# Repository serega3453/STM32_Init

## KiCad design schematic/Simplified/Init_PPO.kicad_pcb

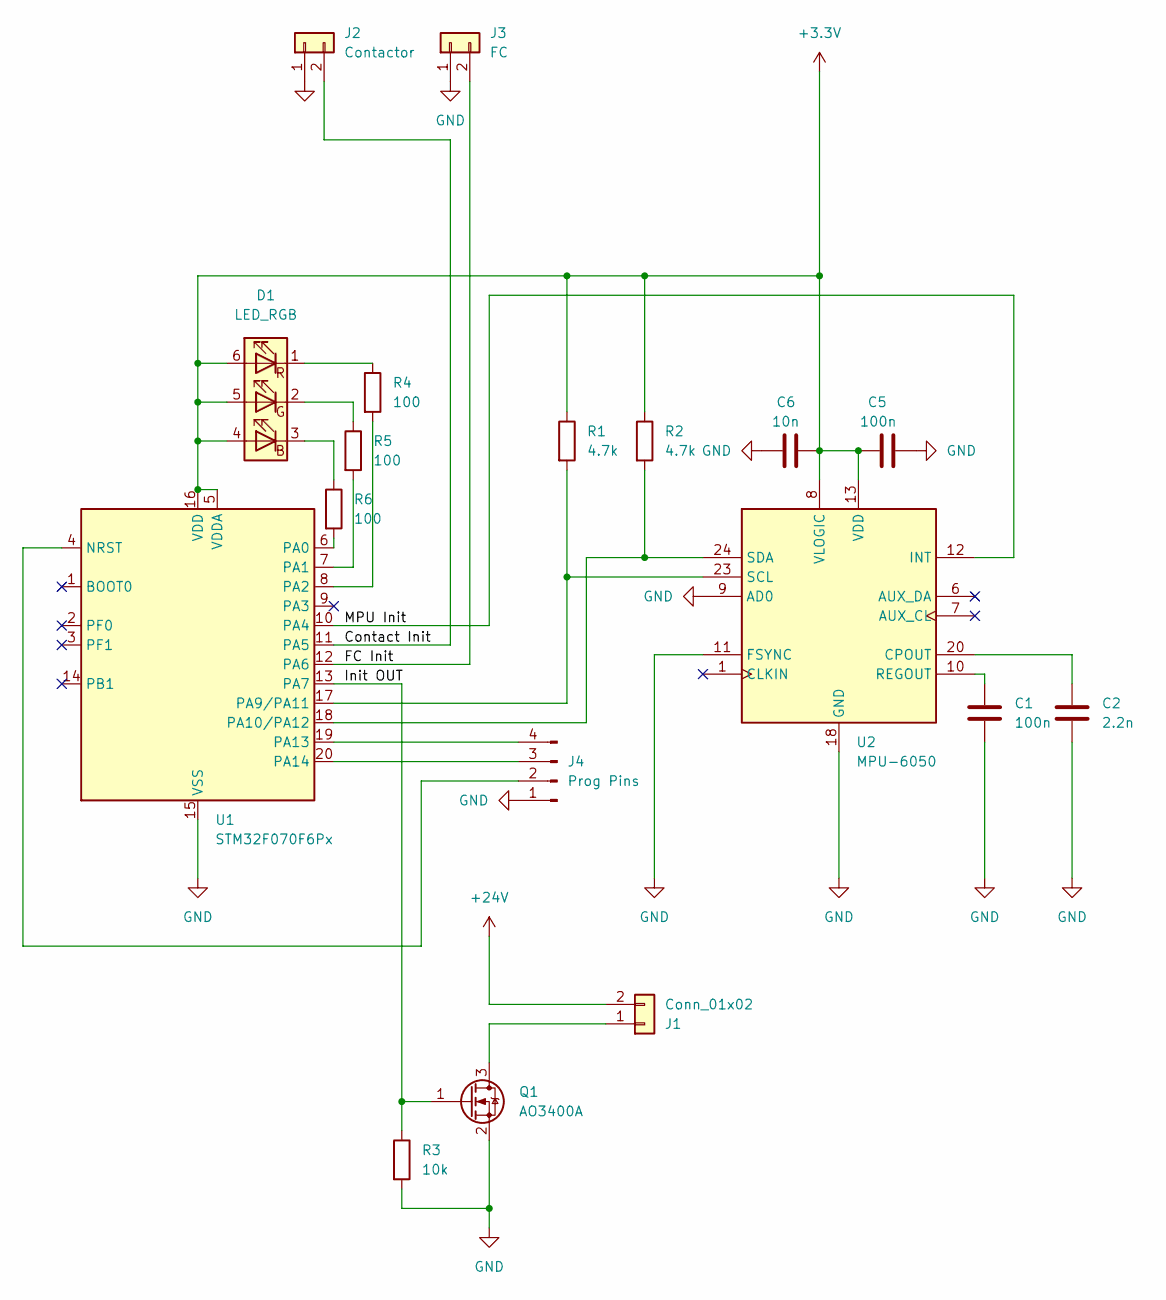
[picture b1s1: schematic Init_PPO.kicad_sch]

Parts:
C1, C5: 100n; C_0805_2012Metric_Pad1.18x1.45mm_HandSolder
C2: 2.2n; C_0805_2012Metric_Pad1.18x1.45mm_HandSolder
C6: 10n; C_0805_2012Metric_Pad1.18x1.45mm_HandSolder
D1: LED_RGB; LED_RGB_5050-6
J1: Conn_01x02; SolderWire-0.25sqmm_1x02_P4.5mm_D0.65mm_OD2mm
J2: Contactor; SolderWire-0.25sqmm_1x02_P4.5mm_D0.65mm_OD2mm
J3: FC; SolderWire-0.25sqmm_1x02_P4.5mm_D0.65mm_OD2mm
J4: Prog Pins
Q1: AO3400A; SOT-23
R1, R2: 4.7k; R_0805_2012Metric_Pad1.20x1.40mm_HandSolder
R3: 10k; R_0805_2012Metric_Pad1.20x1.40mm_HandSolder
R4, R5, R6: 100; R_0805_2012Metric_Pad1.20x1.40mm_HandSolder
U1: STM32F070F6Px; TSSOP-20_4.4x6.5mm_P0.65mm
U2: MPU-6050; InvenSense_QFN-24_4x4mm_P0.5mm

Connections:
+3.3V: C5.1, C6.2, D1.4 (BA), D1.5 (GA), D1.6 (RA), R1.1, R2.1, U1.5 (VDDA), U1.16 (VDD), U2.8 (VLOGIC), U2.13 (VDD)
+24V: J1.2
/Contact Init: J2.2, U1.11 (PA5)
/FC Init: J3.2, U1.12 (PA6)
/Init OUT: Q1.1 (G), R3.1, U1.13 (PA7)
/MPU Init: U1.10 (PA4), U2.12 (INT)
GND: C1.2, C2.2, C5.2, C6.1, J2.1, J3.1, J4.1, Q1.2 (S), R3.2, U1.15 (VSS), U2.9 (AD0), U2.11 (FSYNC), U2.18 (GND)
unnamed: D1.3 (BK), R6.1
unnamed: D1.2 (GK), R5.1
unnamed: D1.1 (RK), R4.1
unnamed: J1.1, Q1.3 (D)
unnamed: J4.2, U1.4 (NRST)
unnamed: J4.3, U1.20 (PA14)
unnamed: J4.4, U1.19 (PA13)
unnamed: R6.2, U1.6 (PA0)
unnamed: R5.2, U1.7 (PA1)
unnamed: R4.2, U1.8 (PA2)
unnamed: R1.2, U1.17 (PA9/PA11), U2.23 (SCL)
unnamed: R2.2, U1.18 (PA10/PA12), U2.24 (SDA)
unnamed: C2.1, U2.20 (CPOUT)
unnamed: C1.1, U2.10 (REGOUT)

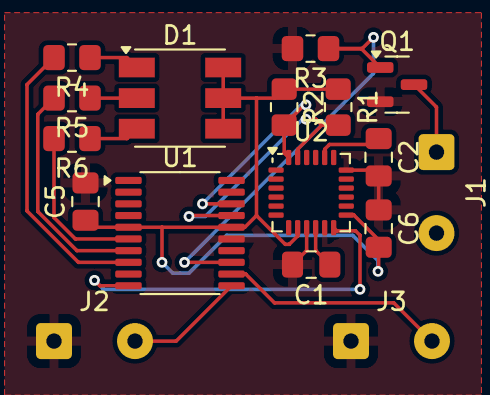
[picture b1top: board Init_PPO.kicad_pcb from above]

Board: 2 copper layers, 17 parts (0 on the bottom side), 17 nets.

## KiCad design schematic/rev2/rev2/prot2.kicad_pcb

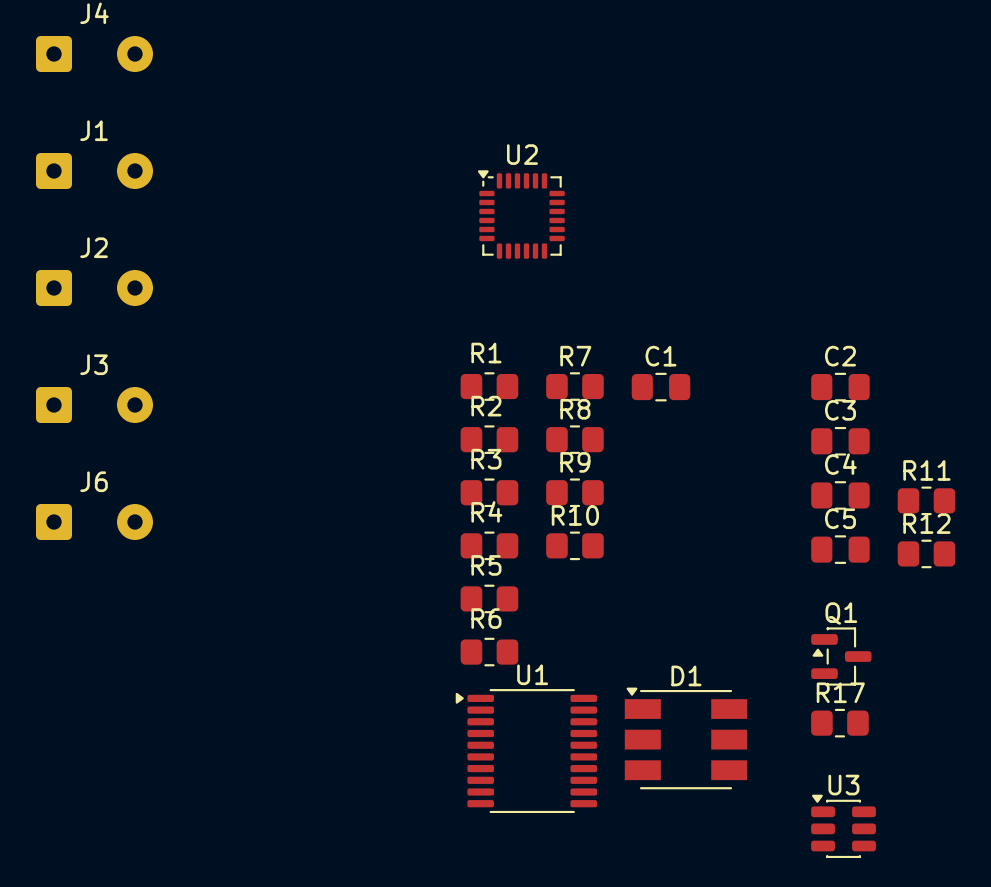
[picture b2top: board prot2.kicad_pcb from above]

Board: 2 copper layers, 28 parts (0 on the bottom side), 21 nets, no tracks yet.

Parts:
C1, C3, C4: 100n; C_0805_2012Metric_Pad1.18x1.45mm_HandSolder
C2: 10n; C_0805_2012Metric_Pad1.18x1.45mm_HandSolder
C5: 2.2n; C_0805_2012Metric_Pad1.18x1.45mm_HandSolder
D1: LED_RGB; LED_RGB_5050-6
J1: SAFE MODE; SolderWire-0.25sqmm_1x02_P4.5mm_D0.65mm_OD2mm
J2: Contactor; SolderWire-0.25sqmm_1x02_P4.5mm_D0.65mm_OD2mm
J3: FCU; SolderWire-0.25sqmm_1x02_P4.5mm_D0.65mm_OD2mm
J4: Power; SolderWire-0.25sqmm_1x02_P4.5mm_D0.65mm_OD2mm
J6: Load; SolderWire-0.25sqmm_1x02_P4.5mm_D0.65mm_OD2mm
Q1: AO3400A; SOT-23
R1, R2, R3, R4, R5, R6, R9, R17: 10k; R_0805_2012Metric_Pad1.20x1.40mm_HandSolder
R7, R8, R10: 100; R_0805_2012Metric_Pad1.20x1.40mm_HandSolder
R11, R12: 4.7k; R_0805_2012Metric_Pad1.20x1.40mm_HandSolder
U1: STM32F070F6Px; TSSOP-20_4.4x6.5mm_P0.65mm
U2: MPU-6050; InvenSense_QFN-24_4x4mm_P0.5mm
U3: TPS54302; SOT-23-6

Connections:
+3.3V: C1.1, C2.2, C3.1, R1.1, R11.1, R12.1, U1.5 (VDDA), U1.16 (VDD), U2.8 (VLOGIC), U2.13 (VDD)
+24V: J4.2, U3.3 (VIN)
/Load switch/LOAD -: J6.2, Q1.3 (D)
Contactor INIT: J2.2, R3.2, U1.7 (PA1)
DATA_RDY: R2.2, U1.6 (PA0), U2.12 (INT)
FCU Init: R4.2, U1.8 (PA2)
GND: C1.2, C2.1, C3.2, C4.2, C5.2, J1.1, J2.1, J3.1, J4.1, Q1.2 (S), R2.1, R3.1, R4.1, R5.1, R6.1, R7.2, R8.2, R9.1, R10.2, R17.2, U1.1 (BOOT0), U1.15 (VSS), U2.9 (AD0), U2.11 (FSYNC), U2.18 (GND), U3.1 (GND)
INIT OUT: Q1.1 (G), R5.2, R17.1, U1.9 (PA3)
LED B: D1.4 (BA), U1.14 (PB1)
LED G: D1.5 (GA), U1.13 (PA7)
LED R: D1.6 (RA), U1.12 (PA6)
unnamed: D1.3 (BK), R7.1
unnamed: D1.2 (GK), R8.1
unnamed: D1.1 (RK), R10.1
unnamed: R1.2, U1.4 (NRST)
unnamed: C5.1, U2.20 (CPOUT)
unnamed: C4.1, U2.10 (REGOUT)
SAFE MODE FCU: J1.2, R6.2, U1.10 (PA4)
SAFE MODE HARD: R9.2, U1.11 (PA5)
SCL: R11.2, U1.3 (PF1), U2.23 (SCL)
SDA: R12.2, U1.2 (PF0), U2.24 (SDA)

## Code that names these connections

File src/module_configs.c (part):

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
/**
 * Configure GPIOA pins for project use:
 * - PA6, PA7: TIM3 PWM outputs (LED channels 0,1) via AF1
 * - PA9, PA10: USART1 TX/RX (AF1) for serial communication
 * - PA0: MPU6050 interrupt input (rising edge)
 * - PA1: Contactor interrupt input (rising edge)
 * - PA2: FCU interrupt input (rising edge)
 * - PA3: Digital output (MOSFET gate control, push-pull, high-speed)
 */
void GPIOA_Config()
{
    /* PA6, PA7 - TIM3 PWM outputs (LED channels) */
    write_bits(&GPIOA_MODER, (0x0FU << 12), (0x0AU << 12));             //PA6_AF && PA7_AF
    write_bits(&GPIOA_OTYPER, (0x03U << 6), (0x00U << 6));              //PA6_PP && PA7_PP
    write_bits(&GPIOA_OSPEEDR, (0x0FU << 12), (0x0FU << 12));           //PA6_HS && PA7_HS
    write_bits(&GPIOA_PUPDR, (0x0FU << 12), (0x00U << 12));             //PA6_PUNPD && PA7_PUNPD
    write_bits(&GPIOA_AFRL, (0xFFU << 24), (0x11U << 24));              //PA6_AF1 && PA7_AF1

    /* PA9, PA10 - USART1 TX/RX (AF1) */
    write_bits(&GPIOA_MODER, (0x0FU << 18), (0x0AU << 18));             //PA9_AF && PA10_AF
    write_bits(&GPIOA_OTYPER, (0x03U << 9), (0x00U << 9));              //push-pull
    write_bits(&GPIOA_OSPEEDR, (0x0FU << 18), (0x0FU << 18));           //high speed
    write_bits(&GPIOA_PUPDR, (0x0FU << 18), (0x04U << 18));             //PA9_NPUNPD, PA10_PU
    write_bits(&GPIOA_AFRH, (0xFFU << 4), (0x11U << 4));                //AF1 для обеих

    //GPIOA PA0 - Input (MPU INT)
    write_bits(&GPIOA_MODER, (0x03U << 0), (0x00U << 0));               //PA0_IN
    write_bits(&GPIOA_OTYPER, (0x01U << 0), (0x00U << 0));              //PA0_PP
    write_bits(&GPIOA_OSPEEDR, (0x03U << 0), (0x03U << 0));             //PA0_HS
    write_bits(&GPIOA_PUPDR, (0x03U << 0), (0x02U << 0));               //PA0_PD

    //GPIOA PA1 - Input (Contactor INT)
    write_bits(&GPIOA_MODER, (0x03U << 2), (0x00U << 2));               //PA1_IN
    write_bits(&GPIOA_OTYPER, (0x01U << 1), (0x00U << 1));              //PA1_PP
    write_bits(&GPIOA_OSPEEDR, (0x03U << 2), (0x03U << 2));             //PA1_HS
    write_bits(&GPIOA_PUPDR, (0x03U << 2), (0x02U << 2));               //PA1_PD

    /* PA2 - Input (FCU INT) */
    write_bits(&GPIOA_MODER,   (0x03U << 4), (0x00U << 4));             //PA2_IN
    write_bits(&GPIOA_OTYPER,  (0x01U << 2), (0x00U << 2));             //PA2_PP
    write_bits(&GPIOA_OSPEEDR, (0x03U << 4), (0x03U << 4));             //PA2_HS
    write_bits(&GPIOA_PUPDR,   (0x03U << 4), (0x02U << 4));             //PA2_PD

    /* PA3 - MOSFET gate output (digital push-pull, high-speed) */
    write_bits(&GPIOA_MODER,   (0x03U << 6), (0x01U << 6));             //PA3_OUT
    write_bits(&GPIOA_OTYPER,  (0x01U << 3), (0x00U << 3));             //PA3_PP (push-pull)
    write_bits(&GPIOA_OSPEEDR, (0x03U << 6), (0x03U << 6));             //PA3_HS (high-speed)
    write_bits(&GPIOA_PUPDR,   (0x03U << 6), (0x00U << 6));             //PA3_NO_PULL

    /* PA4 - Safe mode input from FCU */
    write_bits(&GPIOA_MODER,   (0x03U << 8), (0x00U << 8));             //PA4_IN
    write_bits(&GPIOA_OTYPER,  (0x01U << 4), (0x00U << 4));             //PA4_PP
    write_bits(&GPIOA_OSPEEDR, (0x03U << 8), (0x03U << 8));             //PA4_HS
    write_bits(&GPIOA_PUPDR,   (0x03U << 8), (0x02U << 8));             //PA4_PD

    /* PA5 - Hard safe mode input from reed switch */
    write_bits(&GPIOA_MODER, (0x03U << 10), (0x00U << 10));             //PA5 IN
    write_bits(&GPIOA_OTYPER, (0x01U << 5), (0x00U << 5));              //PA5_PP
    write_bits(&GPIOA_OSPEEDR, (0x03U << 10), (0x03U << 10));           //PA5_HS
    write_bits(&GPIOA_PUPDR, (0x03U << 10), (0x00U << 10));             //PA5_NO_PULL
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
/**
 * Configure GPIOB pins for project use:
 * - PB1: TIM3 PWM output (LED channel 2) via AF1
 */
void GPIOB_Config()
{
    /* PB1 - TIM3 PWM output (LED channel 2) via AF1 */
    write_bits(&GPIOB_MODER, (0x03U << 2), (0x02U << 2));               //PB1_AF
    write_bits(&GPIOB_OTYPER, (0x01U << 1), (0x00U << 1));              //PB1_PP
    write_bits(&GPIOB_OSPEEDR, (0x03U << 2), (0x03U << 2));             //PB1_HS
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
/**
 * Configure GPIOF pins for project use:
 * - PF0, PF1: I2C1 SCL/SDA (open-drain, pull-ups built into I2C bus)
 */
void GPIOF_Config()
{
    /* PF0, PF1 - I2C1 SCL/SDA (open-drain, I2C bus pull-ups required externally) */
    write_bits(&GPIOF_MODER, (0x0FU << 0), (0x0AU << 0));               //PF0_AF && PF1_AF
    write_bits(&GPIOF_OTYPER, (0x03U << 0), (0x03U << 0));              //PF0_OD && PF1_OD
    write_bits(&GPIOF_OSPEEDR, (0x0FU << 0), (0x0FU << 0));             //PF0_HS && PF1_HS
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}

/**
 * Configure EXTI (External Interrupt) for PA0, PA1, PA2.
 * - PA0 (EXTI0): MPU6050 motion detection (rising edge)
 * - PA1 (EXTI1): Contactor interrupt (rising edge)
 * - PA2 (EXTI2): FCU interrupt (rising edge)
 * EXTI0/EXTI1 share EXTI0_1_IRQHandler (IRQ #5)
 * EXTI2/EXTI3 share EXTI2_3_IRQHandler (IRQ #6)
 */
void EXTI_Config(void)
{
    /* Step 1: Connect PA0, PA1, PA2 to EXTI0, EXTI1, EXTI2 lines via SYSCFG */
    /* EXTI0 <- PA0, EXTI1 <- PA1, EXTI2 <- PA2 (port A = 0) */
    write_bits(&SYSCFG_EXTICR1, (0x0FU << 0), (0x00U << 0));            //EXTI0 = Port A (DATA_RDY)
    write_bits(&SYSCFG_EXTICR1, (0x0FU << 4), (0x00U << 4));            //EXTI1 = Port A (Contactor INT)
    write_bits(&SYSCFG_EXTICR1, (0x0FU << 8), (0x00U << 8));            //EXTI2 = Port A (FCU INT)
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    write_bits(&EXTI_RTSR, (1U << 5), (1U << 5));                       //EXTI5: rising edge

    /* Step 3: Enable interrupt requests */
    write_bits(&EXTI_IMR, (1U << 0), (1U << 0));                        //Enable EXTI0 (PA0 DATA_RDY)
    write_bits(&EXTI_IMR, (1U << 1), (1U << 1));                        //Enable EXTI1 (PA1 Contactor INT)
    write_bits(&EXTI_IMR, (1U << 2), (1U << 2));                        //Enable EXTI2 (PA2 FCU INT)
    write_bits(&EXTI_IMR, (1U << 4), (1U << 4));                        //Enable EXTI4 (PA4 safe-mode)
    write_bits(&EXTI_IMR, (1U << 5), (1U << 5));                        //Enable EXTI5 (PA5 hard safe-mode)

    /* Step 4: Enable EXTI0_1_IRQn in NVIC (Nested Vectored Interrupt Controller) */
    /* IRQ #5 for EXTI0_1 */
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
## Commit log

2025-10-23 Init
2025-10-23 Init2
2025-10-24 Init3
2025-10-24 I2C_Problems
2025-11-03 Doesn't work
2025-11-03 GPT new ReadByte()
2025-11-03 I2C Reading Axis
2025-11-03 I2C+USART readings
2025-11-04 G100+cleaning
2025-11-04 Old func
2025-11-04 Refactoring
2025-11-04 More refactoring
2025-11-07 MPU6000 INT implementation
2025-11-07 Even more refactoring
2025-11-07 USART2 -> USART1 (bugged)
2025-12-01 USART1 fix + MPU sensitivity update
2025-12-01 MPU config flexibility
2025-12-01 WOM Settings (to be configured later)
2025-12-01 Adding full schematic
2025-12-01 PA4/PA5 -> PA2/PA3, schematic
2025-12-02 Schematic update
2025-12-03 Full commenting in English
2025-12-03 GPIOA0/1 Interrupts
2025-12-03 PA2 PD
2025-12-03 Addition of TIM14 with 1sec INT, LED colorful blinker
2025-12-03 MPU INT reset
2025-12-03 MPU INT reset on chip reset (INT status reset commented)
2025-12-04 Schematic update + GPIO shuffle + MPU/Contactor/FCU INT
2025-12-04 Schematic
2025-12-05 BOM + schematic changes
2025-12-08 MOSFET Output added
2025-12-11 Schematic + BOM
2025-12-11 WOM reconfigured, red LED added, extra functions romoved
2026-01-07 MPU_WOM debug
2026-01-15 MPU6050 fix, INT on DATA_READY, todo: soft WOM detect
2026-01-16 WOM->soft detect
2026-01-21 Code cleanup, no WOM, starting sequence added
2026-01-21 Added non functional safe mode
2026-01-22 First working build before test
2026-01-22 Working build, better debug, before test
2026-01-22 Small changes
2026-01-26 Serial output changes
2026-01-29 MPU preconfig debug commented
2026-01-29 Good rev, vefore test. better safe mode, better debug
2026-01-29 New build. new debug, new flag management
2026-02-05 new board vatiant begun + asm WFI added in main cycle
2026-02-06 TODO: PA5 - hard safe mode check Added hard safe mode via blocking soft safe mode, reed switch added
2026-02-11 Updated board + PA5 hard safe mode (unchecked)
2026-02-12 Schematic changes
2026-02-17 LED changed from GBR to RGB
2026-02-17 Interrupt fix and schematic fix
2026-02-23 new PA5
2026-02-25 stable build, changed output, added initial check safe mode (doubled), added init on interrupts, fixed pr reading in interrupts
2026-02-27 EXTI2 WIC fix
2026-02-27 Comments, main() small cleanup
2026-02-28 Cpmments + cleanup
2026-03-11 WIP debug
2026-03-11 Minus debug
2026-03-24 MPU preconfigurer change, sensitivity tweaks, I2C driver rework
2026-04-20 Changed timer back to 120s
2026-04-20 Revision+documentation
